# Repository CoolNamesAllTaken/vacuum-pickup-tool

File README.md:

# vacuum-pickup-tool
Vacuum pickup tool for building SMT boards.

## Overview and Description
The Vacuum Pickup Tool is designed to facilitate manual pick-and-place of SMD components onto PCBs, offering faster cycle time than tweezers, since components can be picked directly from their tape.
It consists of a 3d printed case (powered by a 12V barrel jack), a foot pedal (connected to the case by way of a 3.5mm audio cable), and the tool itself (connected to the case by a PVC vacuum tubing).
The "pencil" terminates in a [Luer lock connector](https://en.wikipedia.org/wiki/Luer_taper), a common standard for affixing needles to syringes.

## Parts List
* 1x [12V NC Solenoid Valve](https://www.amazon.com/gp/product/B07BGXMG7H)
* 1x [12V Brushless Vacuum Pump](https://www.ebay.com/itm/US-Stock-Parker-12V-Brushless-Dual-Head-Vacuum-Pump-Diaphragm-Pump-DIY-Air-Pump/392156385546?ssPageName=STRK%3AMEBIDX%3AIT&_trksid=p2057872.m2749.l2649)
* 1x [Male Luer Lock to 3mm or 1/8" Hose Barb Adapter](https://www.ebay.com/itm/Metal-Male-Luer-Lock-Syringe-Fitting-to-3mm-or-1-8-Barb-Hose-ID-43/202463602776?ssPageName=STRK%3AMEBIDX%3AIT&_trksid=p2057872.m2749.l2649)
* 1x [1/6" Hose Barb Tee Fitting](https://www.amazon.com/gp/product/B017UXJ3VG)
* 1x [3/8in Diameter x 12in Aluminum Tube](https://www.ebay.com/itm/K-S-3-8-in-Dia-x-12-in-L-Aluminum-Tube-Round-/383055055746?hash=item592fdc4b82)
* 1x [12V 2-Position 3-Way Solenoid Valve](https://www.amazon.com/uxcell-Miniature-Solenoid-Valve-Positions/dp/B07WS93PCV)
* 1x [12V 1A Power Supply](https://www.amazon.com/gp/product/B00FEOB4EI)
* 1x [Push to Connect Air Hose Fitting](https://www.amazon.com/gp/product/B07H8KPL2W)
* 1x [1/8" ID 1/4" OD Vinyl-Flex Tubing](https://www.amazon.com/gp/product/B00E6BCV0G/ref=ppx_yo_dt_b_asin_title_o01_s02?ie=UTF8&psc=1)
* 1x [Momentary Foot Switch Pedal](https://www.amazon.com/Linemaster-T-91-S-Treadlite-Electrical-Momentary/dp/B002P4XREA)
* 1x [Male to Male 8ft 1/8" Stereo Audio Cable](https://www.amazon.com/AmazonBasics-Stereo-Audio-Cable-Meters/dp/B00NO73Q84)
* 1x [Arduino Nano Clone](https://www.amazon.com/ELEGOO-Arduino-ATmega328P-Without-Compatible/dp/B0713XK923)
* 1x [Adjustable Buck Converter](https://www.amazon.com/Ultra-MP1584EN-Converter-Adjustable-Module/dp/B07SJFTD7F)
* 1x [12V 1A Power Supply (5.5x2.1mm Barrel Jack)](https://www.amazon.com/gp/product/B00FEOB4EI)

## Important Note
The pictures are of an older version of this tool, which has a slightly different PCB that required some extra wire finagling. The air cabling is exactly the same, as are the placements of each part.

## Step 1: Assemble and mount the PCB:
1. Solder all surface mount componenets. In general, going from smallest to largest is advisable so you don't have larger componenets blocking your iron's access to smaller nearby pads.
Keep in mind that diodes and LEDs have polarity! Refer to the pictures or the schematic to see the correct orientation.
2. Solder the male 2pos JST-PH connectors to the board, as well as the barrel jack. Be careful that the JST connectors are in the correct orientation (i.e. the red wire crimped in the female will correspond with the positive side when they are connected.)
3. Set the voltage output of the regulator. We used a bench power supply with alligator clips to supply 12V and a voltmeter with alligator clip leads to read the output voltage. Turn the on-board screw until the output is 5V. It is important to do this before the regulator and the Nano are soldered to the PCB, otherwise the regulator may provide a voltage that fries the Nano's 5V-tolerant pins before it is properly tuned.
4. Solder male headers on the Nano and the regulator. The easist way to get the headers straight up and aligned on the Nano is to place them in a breadboard. This will NOT work for the regulator, as the distances between its holes are inconsistent with a breadboard's.
5. Solder the Nano and regulator to the board.
6. Mount the PCB to the case with four M3 screws and nuts.

## Step 2: Connect the vacuum pump and solenoids:
1. Crimp and affix a female 2pos JST-PH connector to the leads of the vacuum pump. An Engineer PA-09 crimper can be used for this.
2. Crimp and affix a female 2pos JST-PH connector to the leads of each solenoid.
3. Remove the red "hats" from the vacuum pump.
4. Use two short M4 screws to affix the vacuum pump to the top plate of the case.
5. Place one square nut in each of the slots in each top corner of the case. 
6. Screw in a Push-to-Connect Tube Fitting to each of the three holes in the larger solenoid valve. Use a wrench to get them tight, but it is normal for 3ish threads to still extend outside of the hole when it is fully in.
9. Using the tubing and a T-fitting, connect the tubing as shown in the pictures. Leave enough "slack" so that the top (to which the vacuum pump is attached) can be removed without disconnecting the tubing.
8. Use 2 short M4 screws to affix the large solenoid to the bottom of the case.
9. Use a zip tie and a zip tie mount to affix the small solenoid to the bottom of the case.
10. Plug the female JST connectors into the PCB.

## Step 3: Construct and connect the "pencil":
1. Cut the aluminum tube in half, since we want a 6in length. One way to cut it is by placing half in a vise and cutting with a hacksaw, then deburring and filing the rough edges.
2. Cut a long length of the vinyl tubing and feed it through the aluiminum tube.
3. Attach the Luer Lock adapter, and use Kapton tape to slightly increase the diameter of the front of the tube (over the Luer Lock adapter barb) until it makes a nice press fit into the tube.

## Step 4: Wire the foot pedal
1. Chop off the connector from one end of the 3.5mm audio cable. Strip ~1in of the outer cable insulation and ~0.3in of the insulation on each of the 3 inner cables.
2. Use a multimeter to map each internal cable to the sleeve, ring, and tip of the other end's connector. Chop off the wire corresponding to the sleeve; it is unneeded.
3. Unscrew the two side screws of the foot pedal to separate the two main pieces. Take out the plastic insert protecting the internal limit switch.
4. Loosen the two back screws to allow the cable through. Of the two remaining wires, solder one to the Common terminal of the limit switch, and the other to the Normally Open (NO) terminal. It may help to remove the limit switch when doing this. If you have the correct size of quick-connect spade terminals, these could be used to attach wires to the switch instead of soldering.
5. Replace the protective plastic, tighten the two back screws to provide strain relief on the incoming cable, then reattach the sides to each other with the side screws.

## Step 5: Build and flash the code:
1. Download and install Microsoft VSCode and the PlatformIO IDE extension following instructions [here](https://platformio.org/install/ide?install=vscode)
2. In the PlatformIO IDE, click Projects, then Add Existing, and navigate to the `src/vacuum_pickup_tool` directory.
3. In the terminal part of the IDE, run `platformio lib install PinChangeInterrupt`.
4. Plug in the Nano with a USB mini cable, and click the Upload arrow on the bottom bar.
5. If the Upload fails, it may be because different Nano clones use different bootloader versions. To try the other version, go to Projects then click the Configure button next to the Vacuum Pickup Tool project. Scroll down to board and change `nanoatmega328` to `nanoatmega328new`, then try again.

## Step 6: Putting it all together:
1. Plug in the 12V power, the audio cable, and the tubing from the "pencil".
2. When the power is inserted, red LEDs should be on inside the case. When the foot pedal is depressed, the vacuum will activate and a green LED should show inside the case.
3. After releasing the foot pedal, the green LED will turn off but the vacuum pump will remain on for a short period of time, so that if you're picking multiple parts in quick succession you don't have to wait for it to start up each time.

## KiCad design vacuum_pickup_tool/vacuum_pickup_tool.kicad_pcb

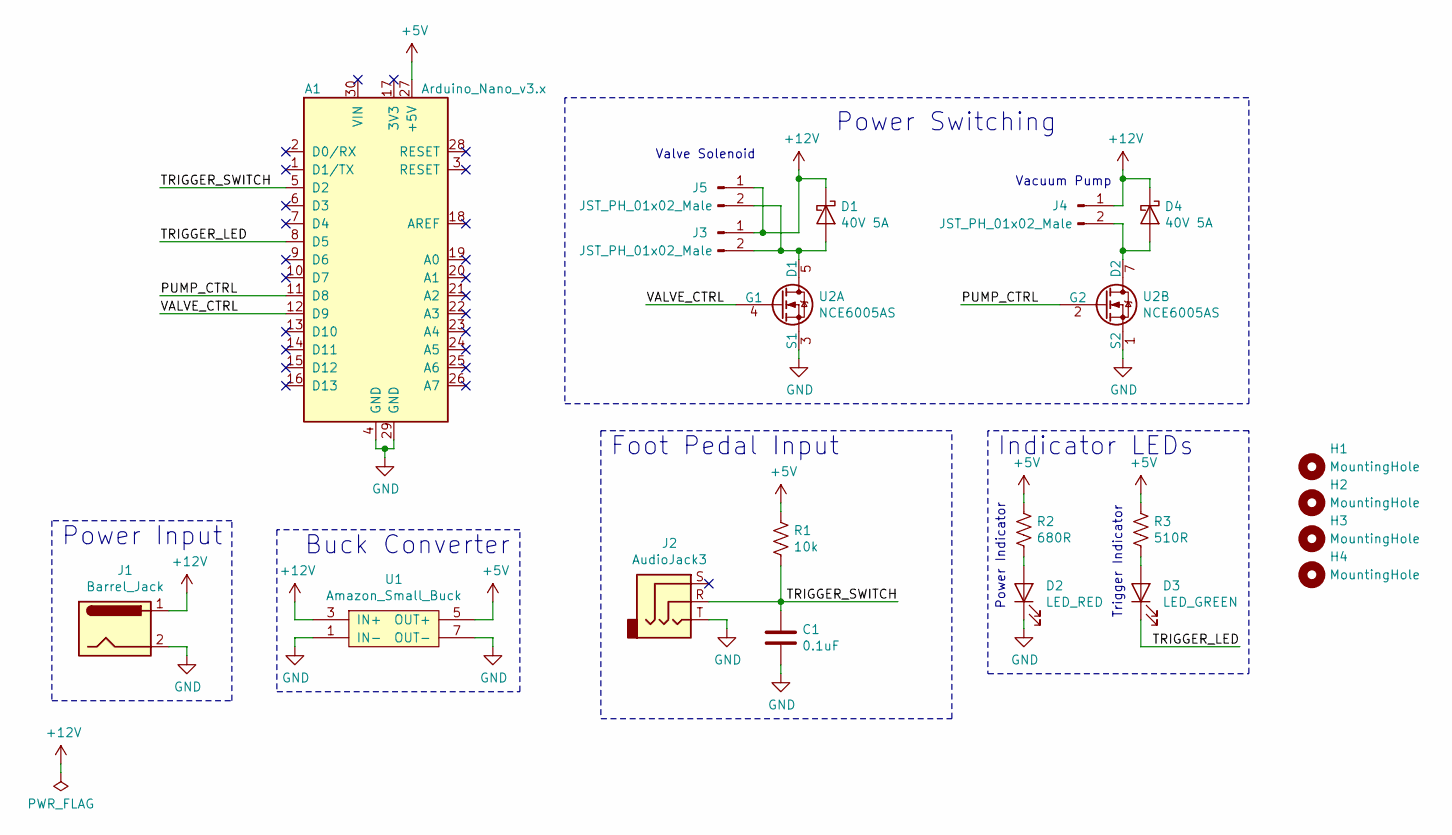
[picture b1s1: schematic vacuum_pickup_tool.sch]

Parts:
A1: Arduino_Nano_v3.x; Arduino_Nano
C1: 0.1uF; C_0603_1608Metric; MPN 0603B104K500NT
D1, D4: 40V 5A; D_SMA; MPN SS54
D2: LED_RED; LED_0603_1608Metric; MPN FC-DA1608HRK-620D
D3: LED_GREEN; LED_0603_1608Metric; MPN FC-DA1608UGK-520D10
H1, H2, H3, H4: MountingHole; MountingHole_3.2mm_M3
J1: Barrel_Jack; SOFNG_DC005-T20; MPN DC005-T20
J2: AudioJack3; Boom_PJ-320B; MPN PJ-320B
J3, J4, J5: JST_PH_01x02_Male; JST_PH_B2B-PH-K_1x02_P2.00mm_Vertical; MPN B2B-PH-K-S(LF)(SN)
R1: 10k; R_0603_1608Metric; MPN RC0603JR-0710KL
R2: 680R; R_0603_1608Metric; MPN 0603WAF6800T5E
R3: 510R; R_0603_1608Metric; MPN RC0603FR-07510RL
U1: Amazon_Small_Buck
U2: NCE6005AS; SOP-8_3.76x4.96mm_P1.27mm; MPN NCE6005AS

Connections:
+5V: A1.27 (+5V), R1.1, R2.1, R3.1, U1.5 (OUT+), U1.6 (OUT+)
+12V: D1.1 (K), D4.1 (K), J1.1, J3.1, J4.1, J5.1, U1.3 (IN+), U1.4 (IN+)
/PUMP_CTRL: A1.11 (D8), U2.2 (G2)
/TRIGGER_LED: A1.8 (D5), D3.1 (K)
/TRIGGER_SWITCH: A1.5 (D2), C1.1, J2.R, R1.2
/VALVE_CTRL: A1.12 (D9), U2.4 (G1)
GND: A1.4 (GND), A1.29 (GND), C1.2, D2.1 (K), J1.2, J2.T, U1.1 (IN-), U1.2 (IN-), U1.7 (OUT-), U1.8 (OUT-), U2.1 (S2), U2.3 (S1)
unnamed: D1.2 (A), J3.2, J5.2, U2.5 (D1), U2.6 (D1)
unnamed: D2.2 (A), R2.2
unnamed: D3.2 (A), R3.2
unnamed: D4.2 (A), J4.2, U2.7 (D2), U2.8 (D2)

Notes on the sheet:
Valve Solenoid
Vacuum Pump
Power Switching
Buck Converter
Power Input
Foot Pedal Input
Power Indicator
Trigger Indicator
Indicator LEDs

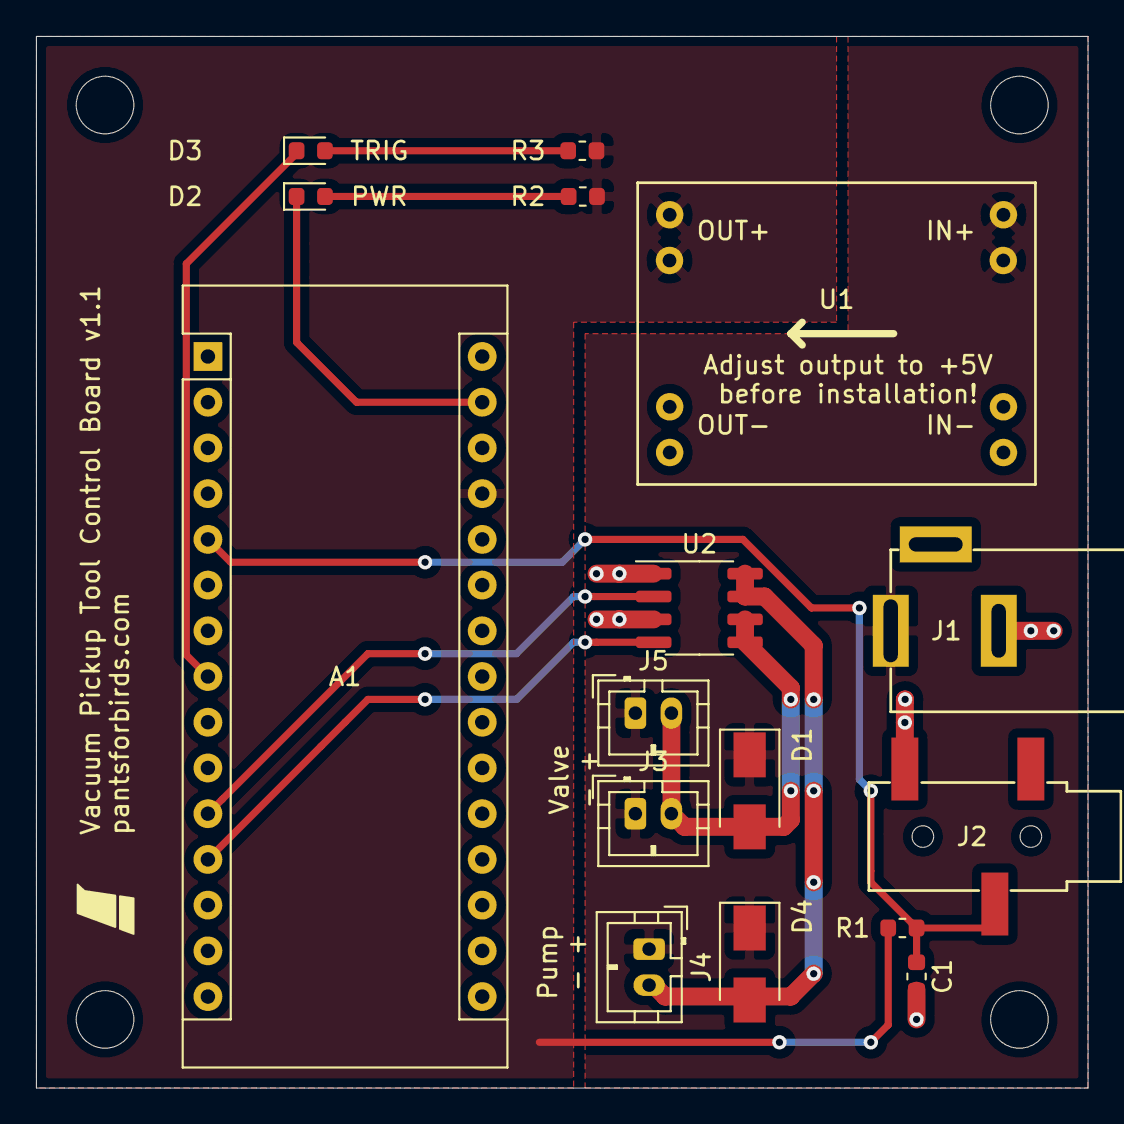
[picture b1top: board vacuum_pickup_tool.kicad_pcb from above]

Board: 2 copper layers, 58.4 x 58.4 mm, 20 parts (0 on the bottom side), 11 nets.

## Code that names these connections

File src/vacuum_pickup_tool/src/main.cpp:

#include <Arduino.h>
#include <PinChangeInterrupt.h>

#define DEBUG

#define TRIGGER_PIN 2
#define TRIGGER_LED_PIN 5
#define PUMP_CTRL_PIN 8
#define VALVE_CTRL_PIN 9

#define VALVE_PWM_DELAY_MS 200 // time after valve trigger until PWMing solenoid
#define VALVE_PWM_DUTY_CYCLE 175 // 0-255, holding current for solenoid valve
#define PUMP_TIMEOUT_MS 5000 // time after last valve trigger that pump turns off

uint32_t last_trigger_time_ms = millis();
bool triggered = false;

void trigger_isr();

void setup() {
  // put your setup code here, to run once:

  #ifdef DEBUG
  Serial.begin(115200);
  #endif

  pinMode(TRIGGER_PIN, INPUT);
  pinMode(TRIGGER_LED_PIN, OUTPUT);
  pinMode(PUMP_CTRL_PIN, OUTPUT);
  pinMode(VALVE_CTRL_PIN, OUTPUT);

  attachPCINT(digitalPinToPCINT(TRIGGER_PIN), trigger_isr, CHANGE);

  digitalWrite(TRIGGER_PIN, LOW);
  digitalWrite(TRIGGER_LED_PIN, HIGH); // inverted
  digitalWrite(PUMP_CTRL_PIN, LOW);
  digitalWrite(VALVE_CTRL_PIN, LOW);
}

void loop() {
  // put your main code here, to run repeatedly:

  if (triggered) {
    // picking up component
    Serial.println("TRIGGERED");
    if (millis() - last_trigger_time_ms > VALVE_PWM_DELAY_MS) {
      // PWM the solenoid for lower holding current
      analogWrite(VALVE_CTRL_PIN, VALVE_PWM_DUTY_CYCLE);
      analogWrite(TRIGGER_LED_PIN, 255 - VALVE_PWM_DUTY_CYCLE);
    } else {
      // solenoid 100% on for initial movement
      digitalWrite(VALVE_CTRL_PIN, HIGH);
      digitalWrite(TRIGGER_LED_PIN, LOW);
    }
  } else {
    // component released
    Serial.println("nah");
    digitalWrite(VALVE_CTRL_PIN, LOW);
    digitalWrite(TRIGGER_LED_PIN, HIGH);

    if (millis() - last_trigger_time_ms > PUMP_TIMEOUT_MS) {
    // turn off pump
    digitalWrite(PUMP_CTRL_PIN, LOW);
  }
  }
}

void trigger_isr() {
  uint8_t trigger = getPinChangeInterruptTrigger(digitalPinToPCINT(TRIGGER_PIN));
  last_trigger_time_ms = millis();

  if (trigger == RISING) {
    // rising edge
    triggered = false;
  } else {
    // falling edge
    triggered = true;
    digitalWrite(PUMP_CTRL_PIN, HIGH);
  }
}

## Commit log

2019-08-29 Make v1.0 of board
2019-09-03 Make v1.0
2019-09-12 Make code for v1.0
2020-07-07 Add hella files and README parts
2020-07-20 Add stls for 3D printed parts
2020-08-17 Modify README and add images
2020-08-17 Add images to README
